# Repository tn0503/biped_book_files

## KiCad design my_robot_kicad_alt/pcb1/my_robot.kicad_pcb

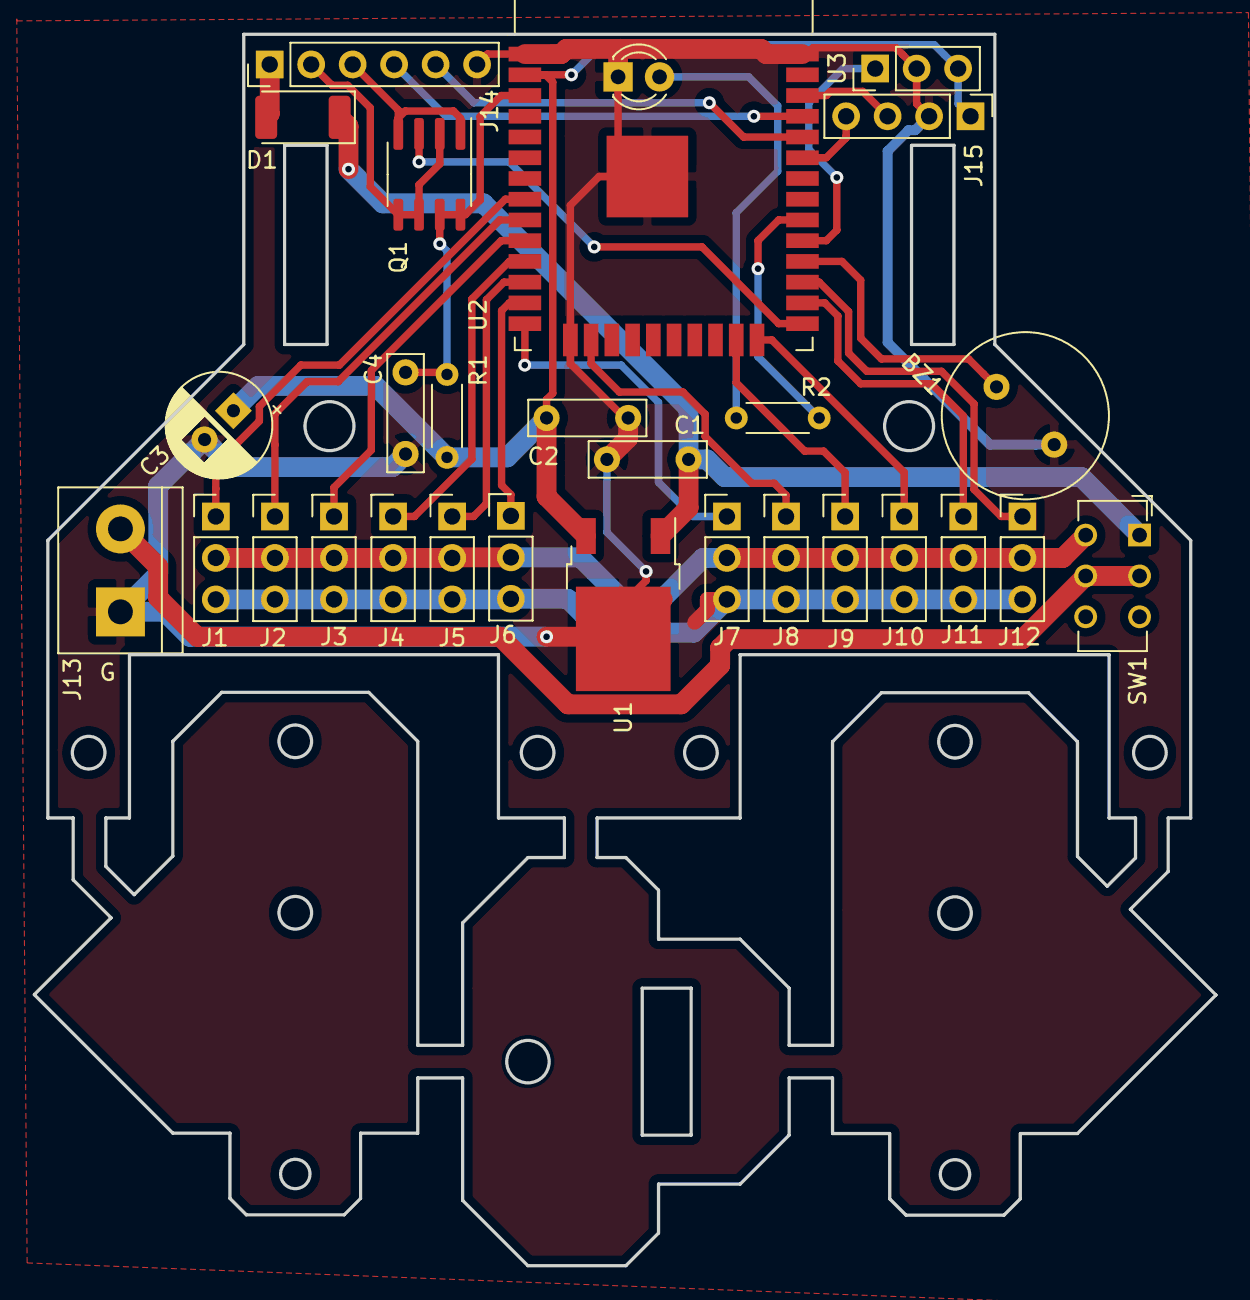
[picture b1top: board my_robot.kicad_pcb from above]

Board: 2 copper layers, 72.4 x 75.4 mm, 29 parts (0 on the bottom side), 30 nets.

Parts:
BZ1: Buzzer; C_Radial_D10.0mm_H12.5mm_P5.00mm
C1: 10u; C_Rect_L7.0mm_W2.0mm_P5.00mm
C2, C4: 0.1u; C_Rect_L7.0mm_W2.0mm_P5.00mm
C3: 47u; CP_Radial_D6.3mm_P2.50mm
D1: D_Schottky; D_2010_5025Metric
D2: LED; LED_D3.0mm
J1, J2, J3, J4, J5, J6, J7, J8, J9, J10, J11, J12: Conn_01x03; PinHeader_1x03_P2.54mm_Vertical
J13: Conn_01x02; TerminalBlock_bornier-2_P5.08mm
J14: Conn_01x06; PinHeader_1x06_P2.54mm_Vertical
J15: Conn_01x04; PinHeader_1x04_P2.54mm_Vertical
Q1: STS2DNE60; SOIC-8_3.9x4.9mm_P1.27mm
R1: 10k; R_Axial_DIN0204_L3.6mm_D1.6mm_P5.08mm_Horizontal
R2: 100; R_Axial_DIN0204_L3.6mm_D1.6mm_P5.08mm_Horizontal
SW1: SW_DPDT_x2; SW_CuK_JS202011CQN_DPDT_Straight
U1: LF33_TO252; TO-252-2
U2: ESP32-WROOM-32
U3: TSDP341xx; PinHeader_1x03_P2.54mm_Vertical

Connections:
+3V3: C2.1, C3.1, J15.1, R1.1, U1.3, U2.2, U3.3
+5V: D1.2, J14.1
+BATT: J1.2, J2.2, J3.2, J4.2, J5.2, J6.2, J7.2, J8.2, J9.2, J10.2, J11.2, J12.2, SW1.4
DTR: J14.2, Q1.2, Q1.5, Q1.6
EN: C4.1, Q1.7, Q1.8, R1.2, U2.3
GND: BZ1.2, C1.2, C2.2, C3.2, C4.2, D2.1, J1.3, J2.3, J3.3, J4.3, J5.3, J6.3, J7.3, J8.3, J9.3, J10.3, J11.3, J12.3, J13.1, J14.6, J15.2, U1.2, U2.1, U2.15, U2.38, U2.39, U3.2
IO0: Q1.3, U2.25
unnamed: BZ1.1, U2.28
unnamed: C1.1, D1.1, SW1.1, U1.1
unnamed: D2.2, R2.2
unnamed: J13.2, SW1.2, SW1.5
unnamed: J14.4, U2.35
unnamed: J14.5, U2.34
unnamed: J15.3, U2.36
unnamed: J15.4, U2.33
unnamed: R2.1, U2.30
unnamed: U2.29, U3.1
RTS: J14.3, Q1.1, Q1.4
SV0: J1.1, U2.8
SV1: J2.1, U2.9
SV2: J3.1, U2.10
SV3: J4.1, U2.11
SV4: J5.1, U2.12
SV5: J6.1, U2.13
SV6: J7.1, U2.14
SV7: J8.1, U2.16
SV8: J9.1, U2.23
SV9: J10.1, U2.24
SV10: J11.1, U2.26
SV11: J12.1, U2.27

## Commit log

2020-09-24 biped book files
    first commit
